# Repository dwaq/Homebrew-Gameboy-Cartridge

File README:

Eagle library, schematic, and board files for a Gameboy Cartridge PCB that uses a Atmel AT49F040 to replace the ROM in a Gameboy cartridge.

Based on Gerry O'Brien's work on a D.I.Y. 512Kb NINTENDO Game Boy Flash Cartridge. 
http://www.digital-circuitry.com/GameBoy.htm

This work is licensed under a Creative Commons Attribution 3.0 Unported License.

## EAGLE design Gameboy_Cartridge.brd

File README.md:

Homebrew-Gameboy-Cartridge
==========================

Eagle library, schematic, and board files for a Gameboy Cartridge PCB that uses a Atmel AT49F040 to replace the ROM in a Gameboy cartridge.

Use the files on the [32kB-variant](https://github.com/dwaq/Homebrew-Gameboy-Cartridge/tree/32kB-variant) branch for a PCB that only supports 32kB ROM images since it does not use an MBC chip.

Based on Gerry O'Brien's work on a D.I.Y. 512Kb NINTENDO Game Boy Flash Cartridge. 
http://www.digital-circuitry.com/GameBoy.htm

This work is licensed under a Creative Commons Attribution 3.0 Unported License.

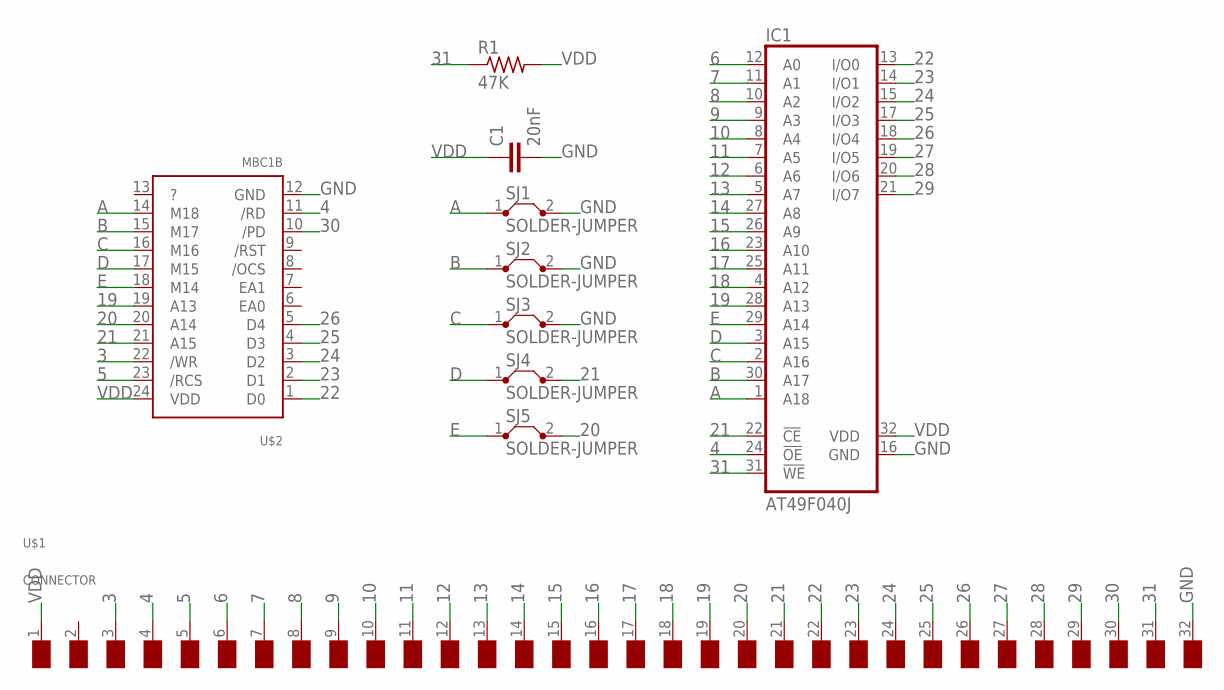
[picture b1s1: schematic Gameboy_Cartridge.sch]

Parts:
C1: 20nF; C0805
IC1: AT49F040J; PLCC32R
R1: 47K; M0805
SJ1, SJ2, SJ3, SJ4, SJ5: SOLDER-JUMPER; SJ
U$1: CONNECTOR
U$2: MBC1B

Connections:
3: U$1.3 (/WR), U$2.22 (/WR)
4: IC1.24 (!OE), U$1.4 (/RD), U$2.11 (/RD)
5: U$1.5 (/RCS), U$2.23 (/RCS)
6: IC1.12 (A0), U$1.6 (A0)
7: IC1.11 (A1), U$1.7 (A1)
8: IC1.10 (A2), U$1.8 (A2)
9: IC1.9 (A3), U$1.9 (A3)
10: IC1.8 (A4), U$1.10 (A4)
11: IC1.7 (A5), U$1.11 (A5)
12: IC1.6 (A6), U$1.12 (A6)
13: IC1.5 (A7), U$1.13 (A7)
14: IC1.27 (A8), U$1.14 (A8)
15: IC1.26 (A9), U$1.15 (A9)
16: IC1.23 (A10), U$1.16 (A10)
17: IC1.25 (A11), U$1.17 (A11)
18: IC1.4 (A12), U$1.18 (A12)
19: IC1.28 (A13), U$1.19 (A13), U$2.19 (A13)
20: SJ5.2, U$1.20 (A14), U$2.20 (A14)
21: IC1.22 (!CE), SJ4.2, U$1.21 (A15), U$2.21 (A15)
22: IC1.13 (I/O0), U$1.22 (D0), U$2.1 (D0)
23: IC1.14 (I/O1), U$1.23 (D1), U$2.2 (D1)
24: IC1.15 (I/O2), U$1.24 (D2), U$2.3 (D2)
25: IC1.17 (I/O3), U$1.25 (D3), U$2.4 (D3)
26: IC1.18 (I/O4), U$1.26 (D4), U$2.5 (D4)
27: IC1.19 (I/O5), U$1.27 (D5)
28: IC1.20 (I/O6), U$1.28 (D6)
29: IC1.21 (I/O7), U$1.29 (D7)
30: U$1.30 (/RS), U$2.10 (/PD)
31: IC1.31 (!WE), R1.1, U$1.31 (VIN)
A: IC1.1 (A18), SJ1.1, U$2.14 (M18)
B: IC1.30 (A17), SJ2.1, U$2.15 (M17)
C: IC1.2 (A16), SJ3.1, U$2.16 (M16)
D: IC1.3 (A15), SJ4.1, U$2.17 (M15)
E: IC1.29 (A14), SJ5.1, U$2.18 (M14)
GND: C1.2, IC1.16 (GND), SJ1.2, SJ2.2, SJ3.2, U$1.32 (GND), U$2.12 (GND)
VDD: C1.1, IC1.32 (VDD), R1.2, U$1.1 (VDD), U$2.24 (VDD)

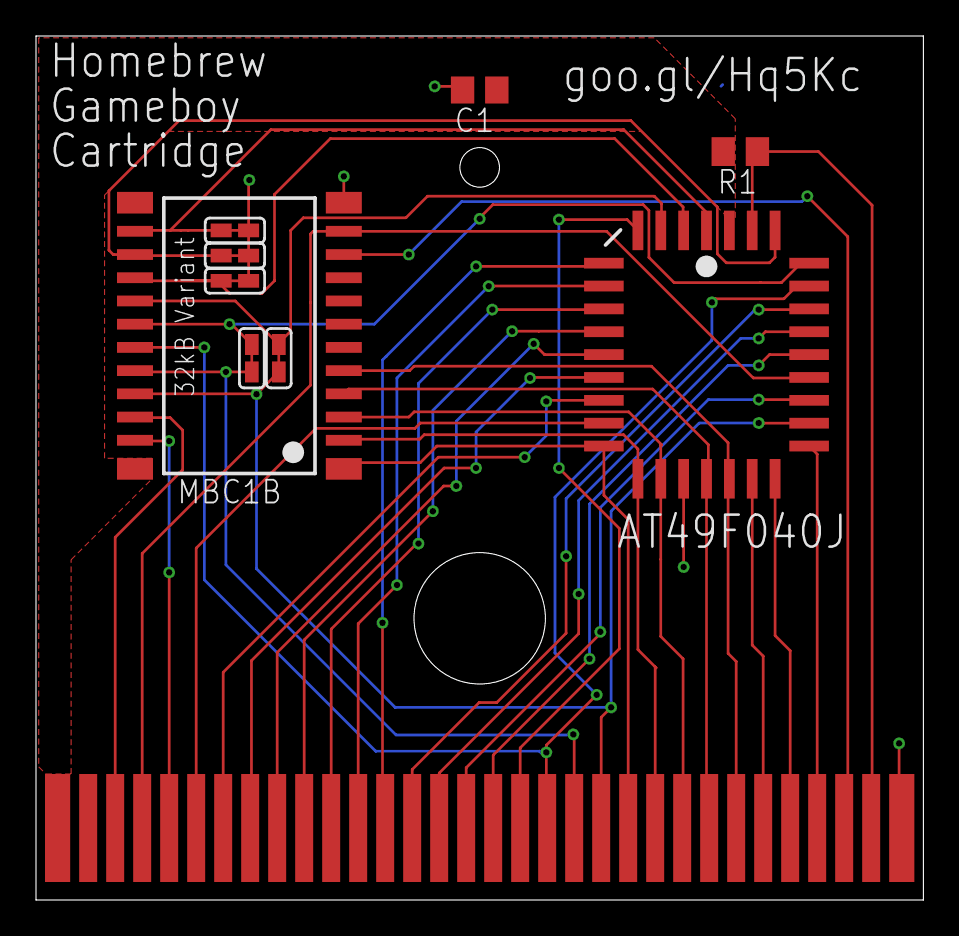
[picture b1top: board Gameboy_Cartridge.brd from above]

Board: 2 copper layers, 49.3 x 48.0 mm, 10 parts (0 on the bottom side), 36 nets.

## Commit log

2012-02-14 creation
2012-02-14 symbol and footprint for gameboy cartridge parts
2012-02-19 added ROM chip and edited pin names for all parts
2012-02-19 renamed VCC pin on ROM to VDD to match other chips
2012-02-19 traces still need routed and maybe a few things fixed, but mostly good
2012-03-04 updated licensing information
2012-03-24 fixed labels for chips, final version
2012-03-24 Files sent to manufacture
2012-05-16 added formatting
2012-05-16 removed old README
2012-06-12 images of eagle files - 600 dpi
2019-04-23 add solder jumpers where traces should be shorted for ROM only operation
2019-04-23 create new SOLDER-JUMPER part that is smaller and default shorted
2019-04-23 replace the solder jumper with my new part
2019-04-23 Fix the connections on the solder jumper
    No ERC errors
2019-04-23 Ripup all traces. Route most of it
2019-04-23 Fixed most of the issues and routed most of it
2019-04-23 Improve the solder jumper footprint
2019-05-02 clean up a ton of traces
2019-05-02 Add VDD pour
2019-05-02 Add GND pour
2019-05-02 Pretty happy with the routing now
2019-05-02 Add text to specify that this special
2019-05-02 Other changes to make it prettier
2019-05-02 Just make the entire bottom the GND plane and adjust VDD pour
2019-05-06 Generate the new Gerber files for 32kB variant
2019-05-06 Link to 32kB variant
2019-06-19 ignore autosaved files
2020-02-13 Move items inside PCB outline
2020-02-13 Update images for 32kB variant - 600 dpi
